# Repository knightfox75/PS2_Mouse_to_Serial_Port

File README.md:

# PS2_Mouse_to_Serial_Port
Un convertidor para conectar un ratón PS/2 a un puerto serie (RS-232).

1. Introducción
--------------------------------------------------------------------------------
Los ratones con conexión DB9 para puerto serie cada vez son más difíciles de encontrar (y más caros), lo que puede suponer un problema si necesitamos emplear uno en un ordenador clásico que solo disponga del puerto serie para su conexión. Después de investigar unas horas, encontré varias opciones comerciales y un par de proyectos open source que, usando placas Arduino, permitían la conexión de un ratón PS/2, o USB compatible con el protocolo PS/2 a un puerto serie.

https://github.com/Lameguy64/ps2serial
 
https://github.com/kristopher/PS2-Mouse-Arduino

Una vez documentado sobre estos proyectos y realizando un primer prototipo funcional de los mismos, decidí realizar mi propia versión del conversor.

2. Como funciona
--------------------------------------------------------------------------------
Básicamente la placa Arduino se encarga de prácticamente todo el trabajo, necesitando solo un poco de electrónica externa para su funcionamiento. Una librería de interacción con el protocolo PS/2 no permite leer la señal codificada procedente del ratón con las entradas. Dicha información se codifica en un paquete de datos en el formato que esperan los drivers de ratón mas comunes y se envían al puerto serie. Además, se monitorea la señal RTS del puerto serie por si se solicita el reinicio del envío de datos.

3. Hardware usado en el prototipo
--------------------------------------------------------------------------------
Se han realizado dos prototipos de prueba, usando las placas Arduino UNO R3 y Arduino NANO, funcionando ambas placas perfectamente. El resto de electrónica sirve para la adaptación de las señales que circulan por el puerto serie, ofreciendo cierto nivel de aislamiento y protección entre este puerto y la placa Arduino. Además, se incorporan dos diodos LED indicadores de estado, para el monitoreo del comportamiento del prototipo.

4. Que indican los LED’s de estado
--------------------------------------------------------------------------------
En mi caso he usado un LED rojo para el indicador de alimentación y un LED amarillo para el indicador de estado. Dicho indicador nos proporciona cierta información en el momento del arranque del adaptador, así como de su funcionamiento. Al encender el adaptador, si no puede detectar un ratón compatible conectado, quedará encendido de manera permanente. Dicho LED de estado parpadeará de manera intermitente una vez por segundo si ha detectado un ratón, pero no es posible iniciar la comunicación siguiendo el protocolo PS/2. Si el proceso de inicio se realiza correctamente, este LED emitirá 3 parpadeos, uno largo seguido de 2 mas cortos. Una vez iniciado el adaptador, si movemos el ratón, observaremos que este LED parpadea regularmente, quedando encendido mientras mantengamos pulsado alguno de los 3 botones del ratón. Si movemos la rueda de scroll, tambien emitira un parpadeo.
Si se recibe desde el puerto serie la señal RTS, este LED emitirá un parpadeo de aproximadamente medio segundo. Esto nos permite verificar que el driver ha detectado correctamente nuestro adaptador.

5. Capacidades extendidas
--------------------------------------------------------------------------------
Dado que este proyecto (en especial la placa ISA) está destinado a ordenadores sin puerto PS/2 (normalmente 486 y anteriores), usando el sistema operativo MS-DOS o Windows 3.11 y anteriores, junto con el hecho de que actualmente casi todos los ratones PS/2 son ópticos y disponen de la rueda de scroll, sumándole que para estos ordenadores casi ningún programa hace uso de la rueda de scroll, he decidido usar dicha rueda para ajustar a tiempo real la velocidad de desplazamiento del cursor. Dado que, según la resolución de pantalla, programa o modelo de ratón esta puede ser diferente, creo que es una característica útil. La velocidad seleccionada se conservará hasta que apaguemos el adaptador (o el ordenador en el caso de la placa ISA), no viendose afectada por el reinicio del sistema. Si queremos guardar la velocidad actual de manera permanente, deberemos de mantener pulsados los botones izquierdo y derecho de manera simultanea durante 5 segundos, observando que el LED de estado se apaga transcurrido ese tiempo. Esto nos indica que la configuración de ha almacenado de manera correcta. Si en algún momento deseamos restaurar la configuración por defecto, deberemos de mantener presionados ambos botones durante 10 segundos, el LED de estado se apagará a los 5 segundos, volviéndose a encender transcurridos 10 segundos. Esto indicará que la configuración se ha restaurado y almacenado con éxito.

6. Precauciones
--------------------------------------------------------------------------------
- Conectar y desconectar siempre el ratón al puerto PS/2 con el adaptador desconectado. La conexión o desconexión del ratón con el adaptador conectado a la alimentación podría causar daños al ratón y al propio adaptador. Esto también se aplica a la conexión del adaptador con el puerto serie del ordenador, siendo muy recomendable que todas las conexiones se realicen con los equipos apagados.
- Cualquier dispositivo conectado al puerto RS-232 del ordenador puede causar daños a dicho puerto o al dispositivo si este tiene algún error de montaje, por lo que se recomienda que repaséis 3 veces las conexiones antes de conectarlo a vuestro ordenador.
- Aplicable a la versión ISA, en ningún caso actualicéis el firmware del modulo Arduino con la tarjeta ISA insertada en la placa base. Retirar la tarjeta ISA o el módulo Arduino antes de conectarlo al puerto USB para su actualización. De no hacerlo, se corre el riesgo de dañar el módulo Arduino la propia placa base del ordenador.

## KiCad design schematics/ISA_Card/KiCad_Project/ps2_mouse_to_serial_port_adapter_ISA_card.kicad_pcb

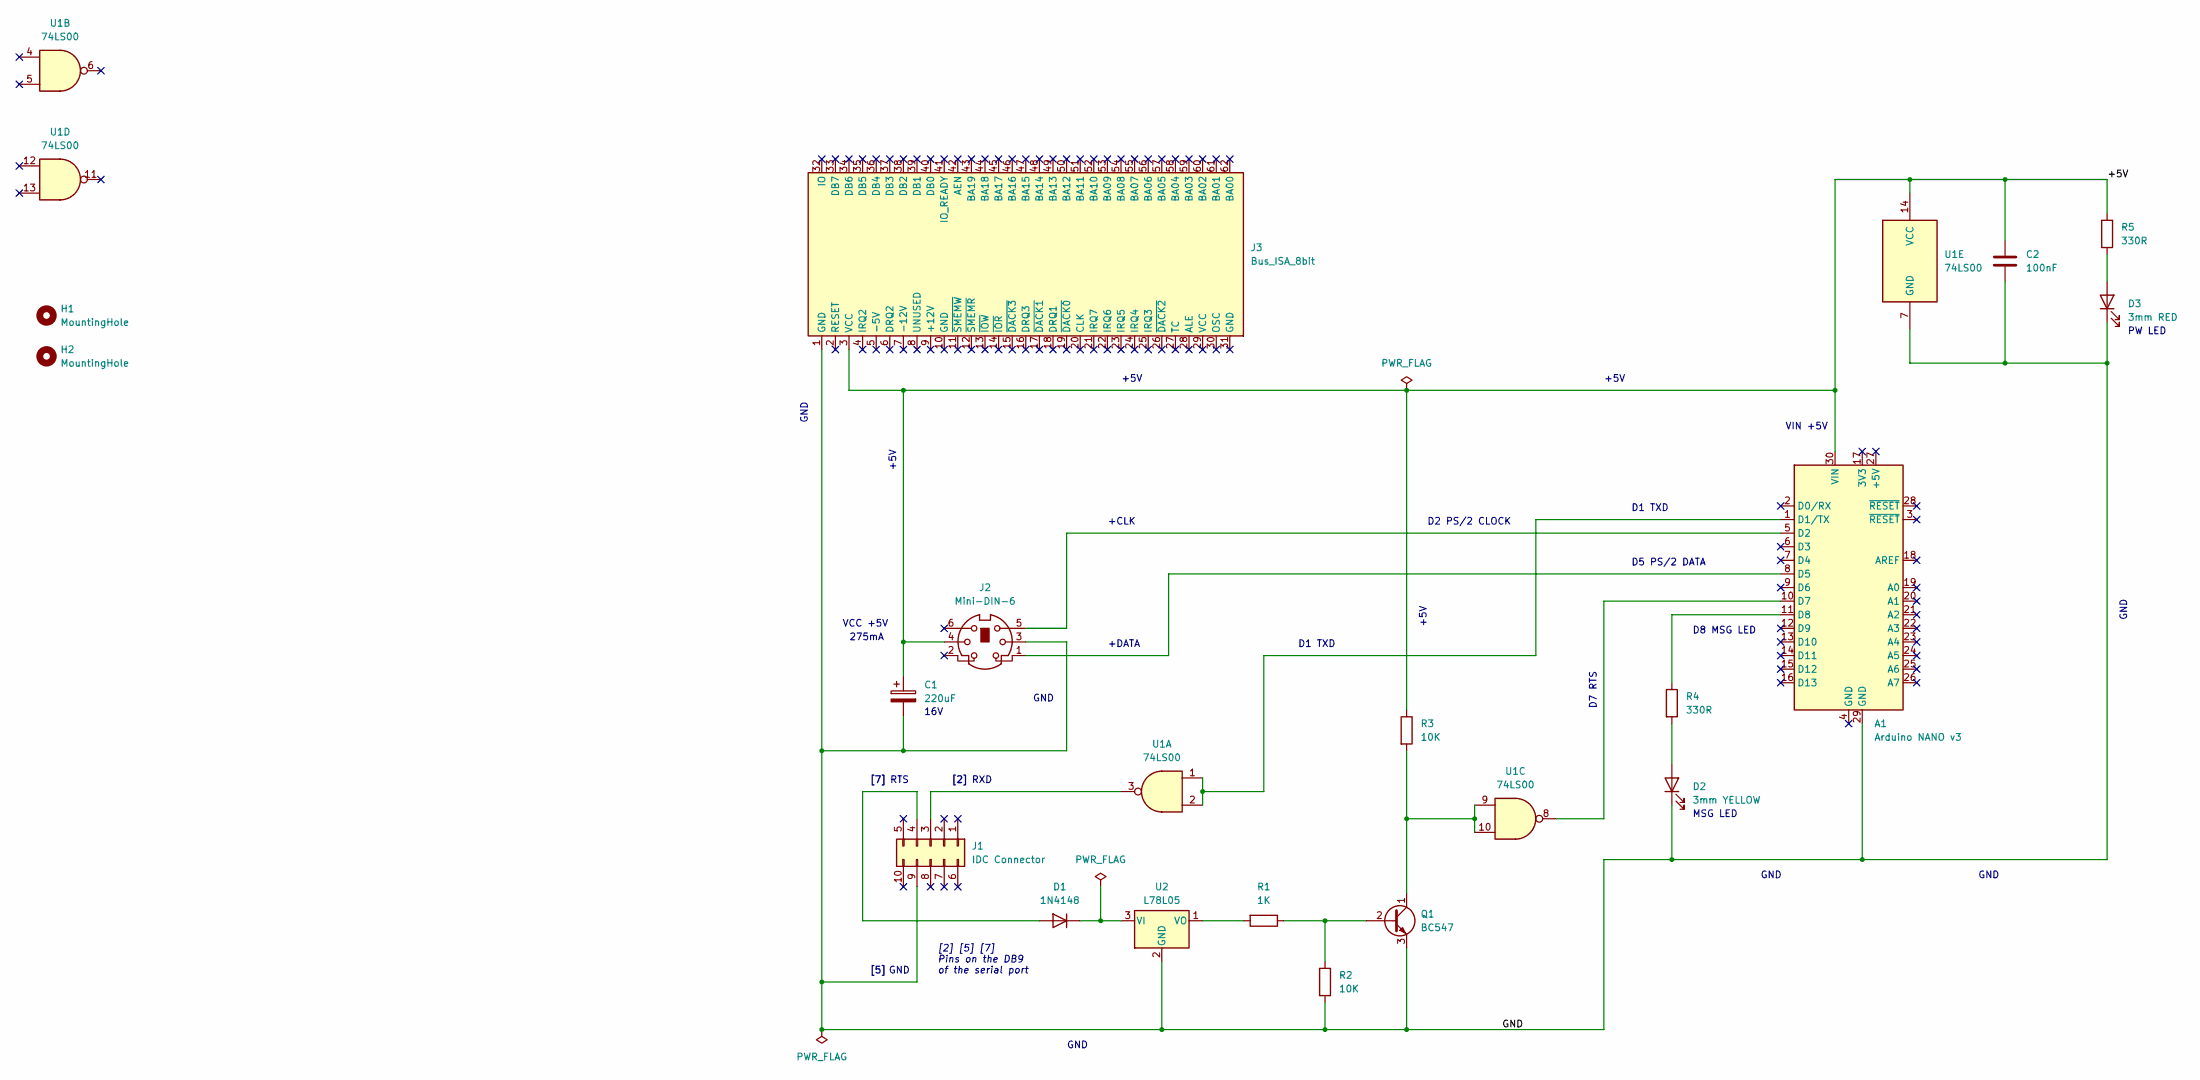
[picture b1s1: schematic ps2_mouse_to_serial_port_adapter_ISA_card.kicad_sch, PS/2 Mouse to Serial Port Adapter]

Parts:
A1: Arduino NANO v3; Arduino_Nano
C1: 220uF; CP_Radial_D8.0mm_P3.80mm
C2: 100nF; C_Disc_D6.0mm_W2.5mm_P5.00mm
D1: 1N4148; D_DO-35_SOD27_P7.62mm_Horizontal
D2: 3mm YELLOW; LED_D3.0mm
D3: 3mm RED; LED_D3.0mm
H1, H2: MountingHole; MountingHole_3.2mm_M3
J1: IDC Connector; IDC-Header_2x05_P2.54mm_Horizontal
J2: Mini-DIN-6; Connector_Mini_DIN_6pin
J3: Bus_ISA_8bit; BUS_AT_ISA_8BITS
Q1: BC547; TO-92_HandSolder
R1: 1K; R_Axial_DIN0207_L6.3mm_D2.5mm_P7.62mm_Horizontal
R2, R3: 10K; R_Axial_DIN0207_L6.3mm_D2.5mm_P7.62mm_Horizontal
R4, R5: 330R; R_Axial_DIN0207_L6.3mm_D2.5mm_P7.62mm_Horizontal
U1: 74LS00; DIP-14_W7.62mm_Socket
U2: L78L05; TO-92_HandSolder

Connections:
/+5V: A1.30 (VIN), C1.1, C2.1, J2.4, J3.3 (VCC), R3.1, R5.1, U1.14 (VCC)
/GND: A1.29 (GND), C1.2, C2.2, D2.1 (K), D3.1 (K), J1.9, J2.3, J2.GND, J3.1 (GND), Q1.3 (E), R2.2, U1.7 (GND), U2.2 (GND)
unnamed: A1.1 (D1/TX), U1.1, U1.2
unnamed: A1.5 (D2), J2.5
unnamed: A1.8 (D5), J2.1
unnamed: A1.10 (D7), U1.8
unnamed: A1.11 (D8), R4.1
unnamed: D1.2 (A), J1.4
unnamed: D1.1 (K), U2.3 (VI)
unnamed: D2.2 (A), R4.2
unnamed: D3.2 (A), R5.2
unnamed: J1.3, U1.3
unnamed: Q1.2 (B), R1.1, R2.1
unnamed: Q1.1 (C), R3.2, U1.9, U1.10
unnamed: R1.2, U2.1 (VO)

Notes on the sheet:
+CLK
PW LED
GND
[5]
[2]
VCC +5V
[2] [5] [7] Pins on the DB9 of the serial port
16V
MSG LED
+5V
D8 MSG LED
RTS
D5 PS/2 DATA
D1 TXD
D2 PS/2 CLOCK
VIN +5V
RXD
D7 RTS
[7]
+DATA
275mA

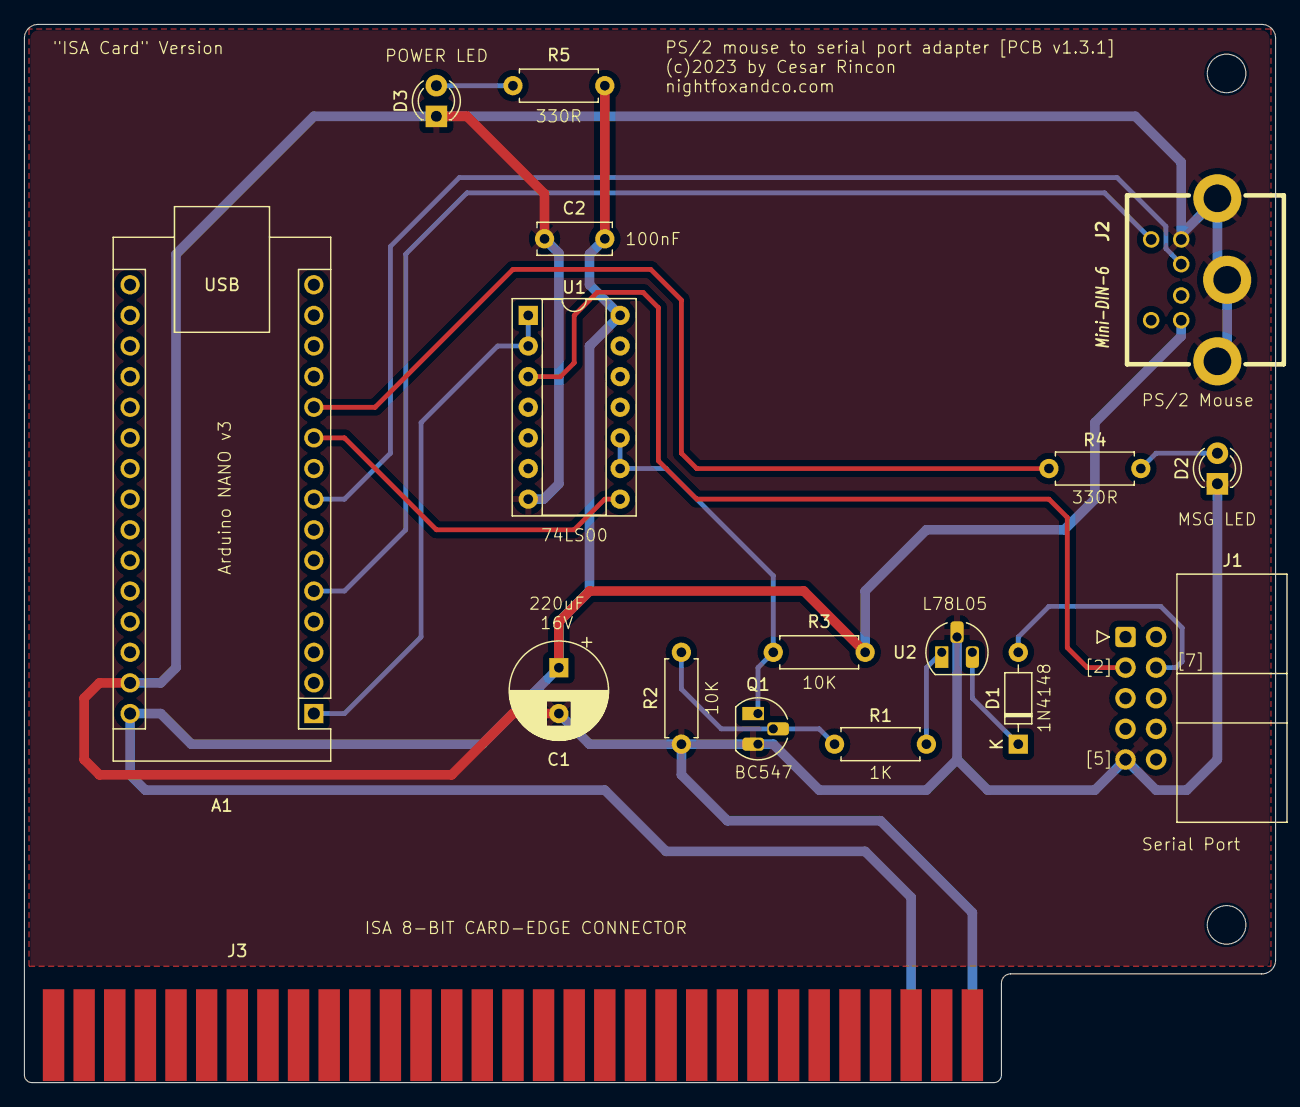
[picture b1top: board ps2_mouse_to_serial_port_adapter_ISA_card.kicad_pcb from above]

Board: 2 copper layers, 103.8 x 87.8 mm, 19 parts (0 on the bottom side), 15 nets.

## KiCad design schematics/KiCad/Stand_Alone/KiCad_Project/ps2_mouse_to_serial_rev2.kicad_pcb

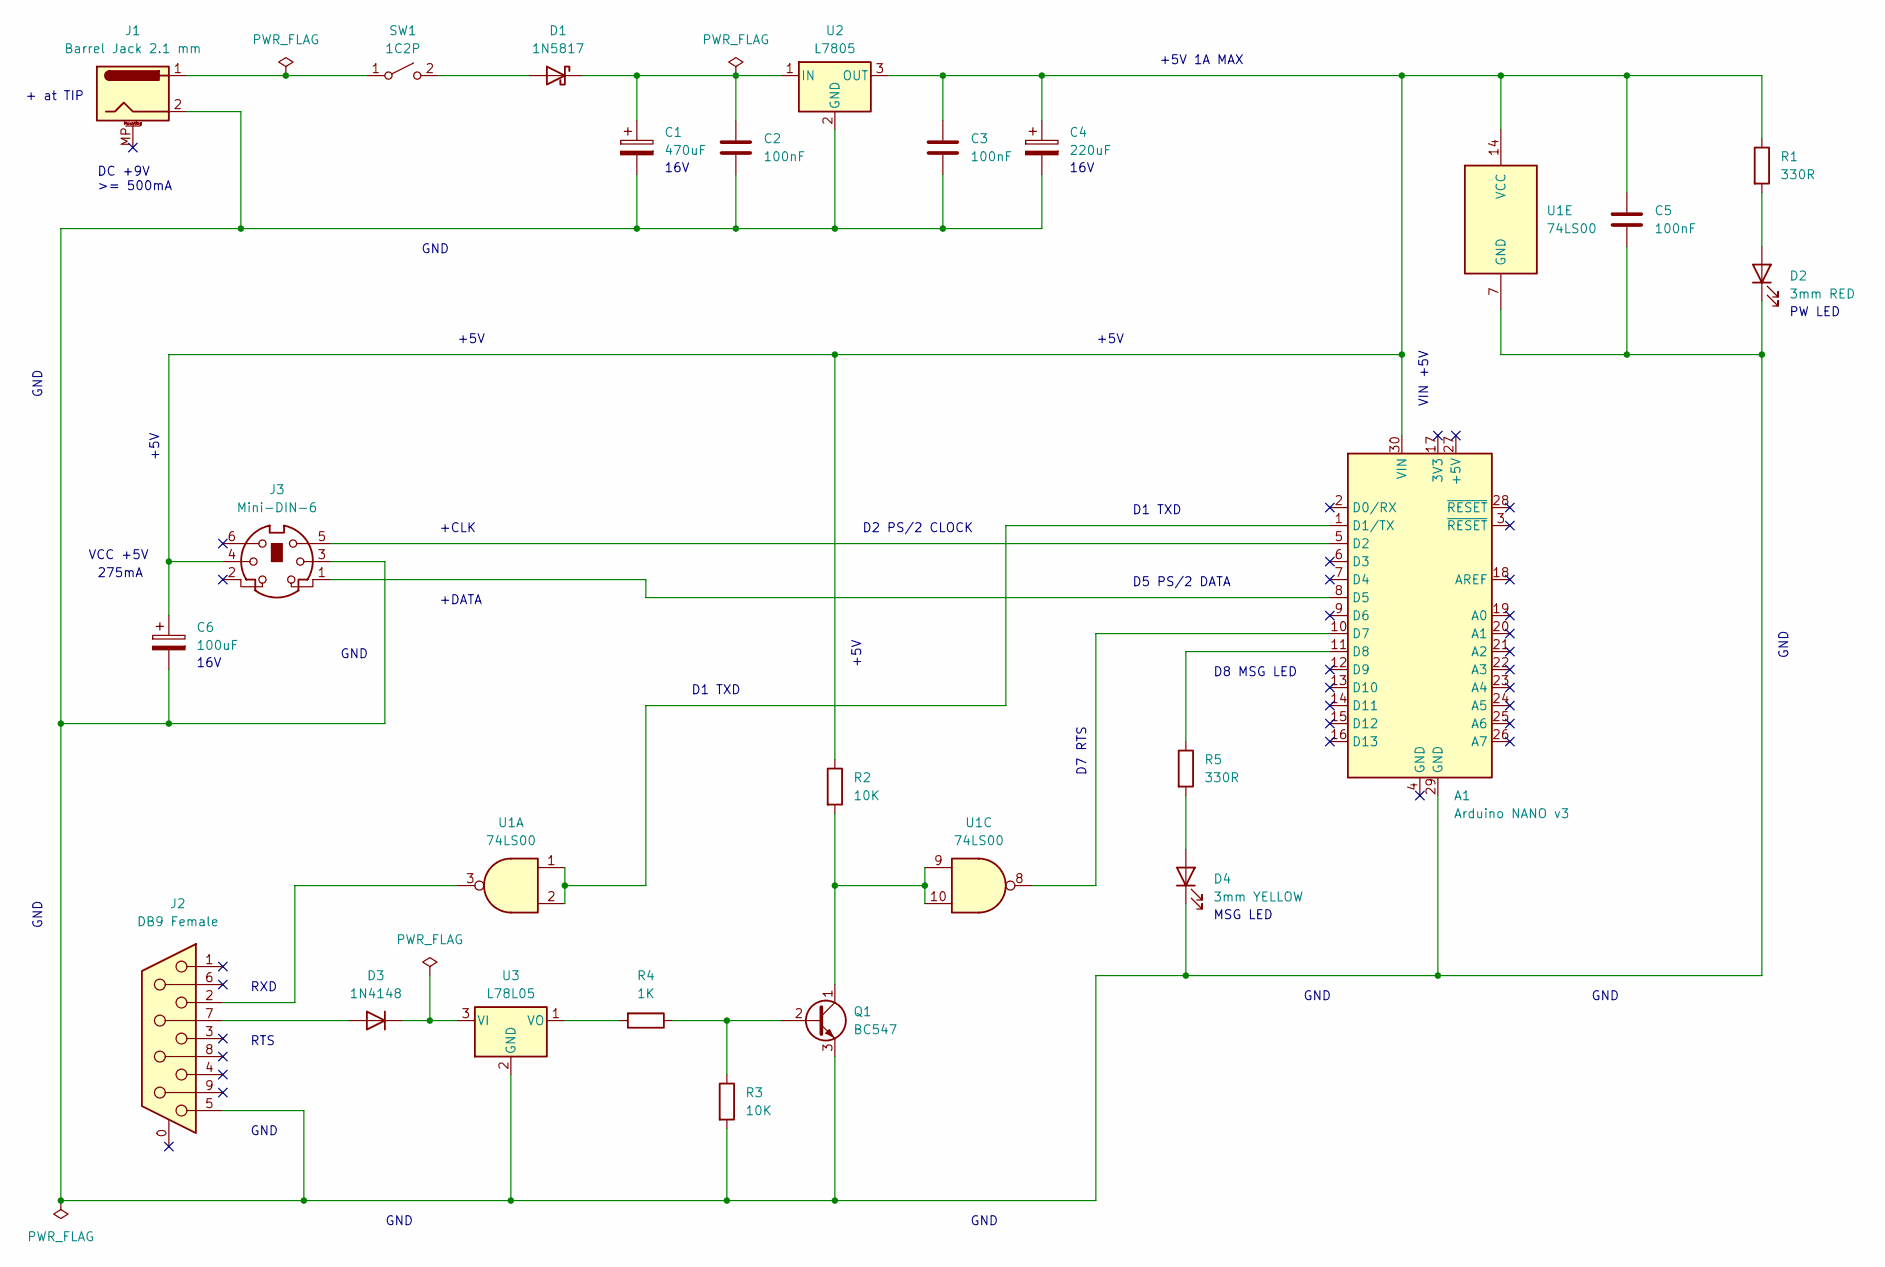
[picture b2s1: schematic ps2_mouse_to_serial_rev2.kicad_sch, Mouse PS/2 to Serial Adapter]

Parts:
A1: Arduino NANO v3; Arduino_Nano
C1: 470uF; CP_Radial_D8.0mm_P3.80mm
C2, C3, C5: 100nF; C_Disc_D6.0mm_W2.5mm_P5.00mm
C4: 220uF; CP_Radial_D8.0mm_P3.80mm
C6: 100uF; CP_Radial_D8.0mm_P3.80mm
D1: 1N5817; D_DO-41_SOD81_P10.16mm_Horizontal
D2: 3mm RED; LED_D3.0mm
D3: 1N4148; D_DO-35_SOD27_P7.62mm_Horizontal
D4: 3mm YELLOW; LED_D3.0mm
J1: Barrel Jack 2.1 mm; BarrelJack_Horizontal
J2: DB9 Female; DSUB-9_Female_Horizontal_P2.77x2.84mm_EdgePinOffset4.94mm_H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
J3: Mini-DIN-6; Conn_Mini_DIN_6pin
Q1: BC547; TO-92_Inline
R1, R5: 330R; R_Axial_DIN0207_L6.3mm_D2.5mm_P7.62mm_Horizontal
R2, R3: 10K; R_Axial_DIN0207_L6.3mm_D2.5mm_P7.62mm_Horizontal
R4: 1K; R_Axial_DIN0207_L6.3mm_D2.5mm_P7.62mm_Horizontal
SW1: 1C2P; TerminalBlock_TE_282834-2_1x02_P2.54mm_Horizontal
U1: 74LS00; DIP-14_W7.62mm_Socket
U2: L7805; TO-220-3_Vertical
U3: L78L05; TO-92_Inline

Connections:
unnamed: A1.1 (D1/TX), U1.1, U1.2
unnamed: A1.5 (D2), J3.5
unnamed: A1.8 (D5), J3.1
unnamed: A1.10 (D7), U1.8
unnamed: A1.11 (D8), R5.1
unnamed: A1.30 (VIN), C3.1, C4.1, C5.1, C6.1, J3.4, R1.1, R2.1, U1.14 (VCC), U2.3 (OUT)
unnamed: D1.2 (A), SW1.2 (B)
unnamed: C1.1, C2.1, D1.1 (K), U2.1 (IN)
unnamed: D2.2 (A), R1.2
unnamed: A1.29 (GND), C1.2, C2.2, C3.2, C4.2, C5.2, C6.2, D2.1 (K), D4.1 (K), J1.2, J2.5, J3.3, Q1.3 (E), R3.2, U1.7 (GND), U2.2 (GND), U3.2 (GND)
unnamed: D3.2 (A), J2.7
unnamed: D3.1 (K), U3.3 (VI)
unnamed: D4.2 (A), R5.2
unnamed: J2.2, U1.3
unnamed: Q1.2 (B), R3.1, R4.1
unnamed: Q1.1 (C), R2.2, U1.9, U1.10
unnamed: J1.1, SW1.1 (A)
unnamed: R4.2, U3.1 (VO)

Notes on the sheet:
+CLK
PW LED
GND
16V
VCC +5V
MSG LED
+5V
D8 MSG LED
DC +9V >= 500mA
RTS
D5 PS/2 DATA
D1 TXD
D2 PS/2 CLOCK
+ at TIP
VIN +5V
RXD
D7 RTS
+5V 1A MAX
+DATA
275mA

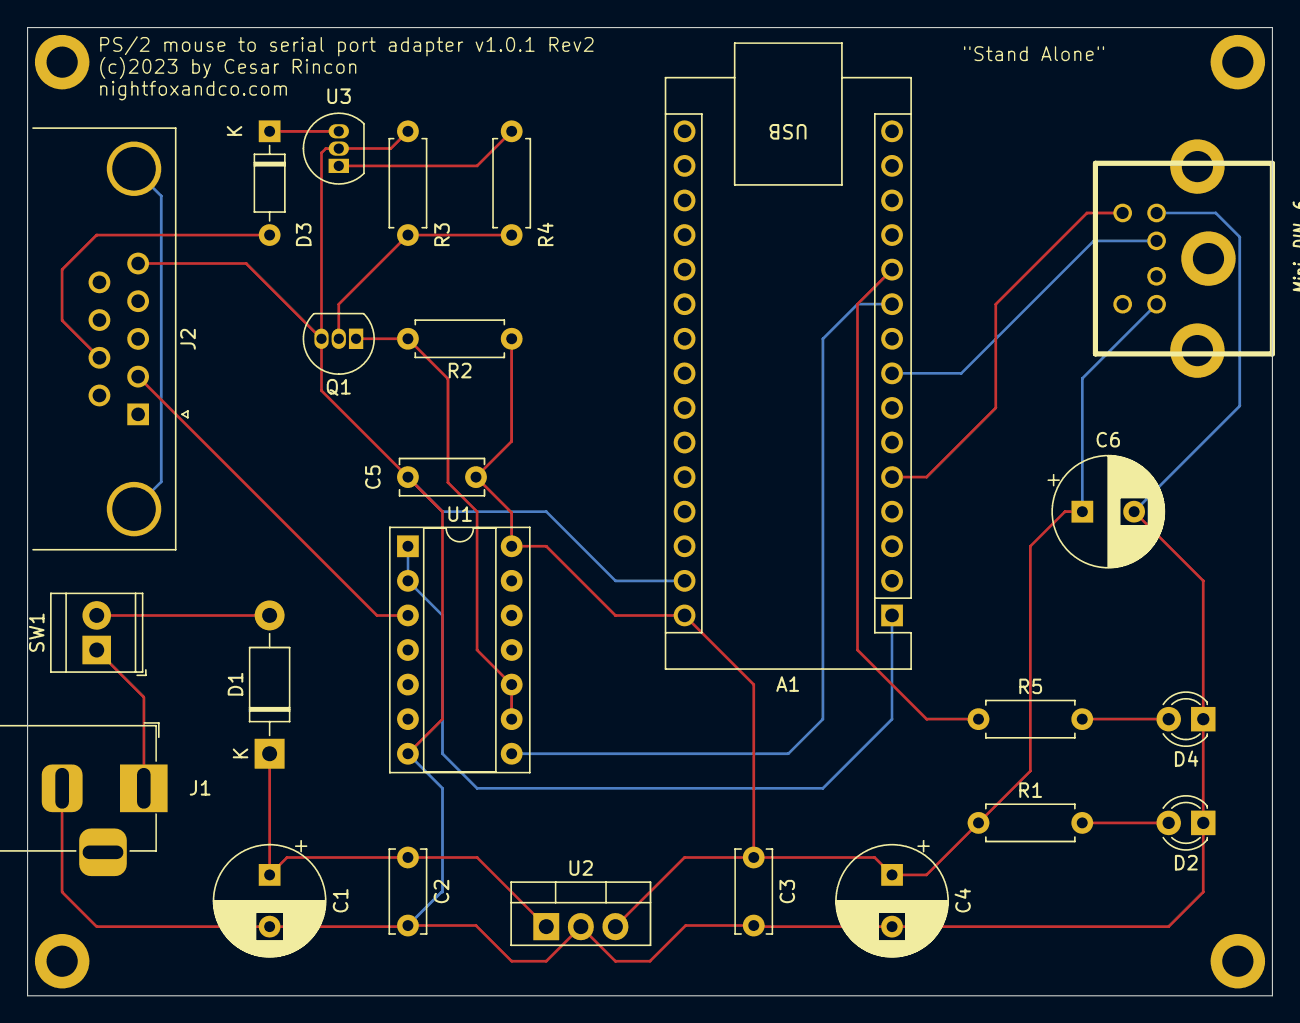
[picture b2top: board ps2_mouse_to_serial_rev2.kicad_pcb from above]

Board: 2 copper layers, 91.4 x 71.1 mm, 24 parts (0 on the bottom side), 18 nets.

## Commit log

2023-07-26 PS/2 Mouse to Serial v0.9.0-beta
    Initial release.
2023-08-08 V1.0.0-stable
    - Modificado el esquema, añadiendo una fuente de alimentación opcional y un diodo de protección en la entrada de la señal RTS del puerto serie.
    - No hay cambios en el código.
    - Verificado el funcionamiento del prototipo con éxito en los siguientes
    equipos y configuraciones:
    · Amstrad PC1512, MS-DOS 6.22, CuteMouse 1.91 & MS Mouse 11
    · Philips NMS9100, MS-DOS 6.22, CuteMouse 1.91 & MS Mouse 11
2023-08-09 V1.0.1-rev2
    - Se añade el esquema realizado en formato KiCad.
    - Corregido un error en la conexión a masa del condensador C6 en el esquema en formato TinyCad.
    - Modificadas algunas de las anotaciones en los pins de Arduino en el esquema en formato TinyCad.
    - Añadidos los esquemas de KiCad en formato PDF y PNG.
    - No hay cambios en el código.
2023-08-10 v1.0.1-rev2
    - Se añade el esquema realizado en formato KiCad.
    - Corregido un error en la conexión a masa del condensador C6 en el esquema en formato TinyCad.
    - Modificadas algunas de las anotaciones en los pins de Arduino en el esquema en formato TinyCad.
    - Añadidos los esquemas de KiCad en formato PDF y PNG.
    - Añadidos los diseños de las PBC para las version "Stand Alone" y "In-a-Box". Estos diseños se han mandado a producción, pero aún no se han verificado.
    - No hay cambios en el código.
2023-08-11 V1.0.1-rev2.1
    - Corregido un error en la colocación del conector PS/2 en la placa "Stand Alone" del proyecto KiCad.
    - Recordar que aún no he podido producir físicamente estas placas, por lo que si vais a producirlas, revisar el proyecto 3 veces en búsqueda de errores.
2023-08-12 v1.3.0
    - Se utiliza una referencia de versión para el proyecto, independientemente de las versiones de placa o software para facilitar la identificación de la versión actual.
    - Se añade el esquema y diseño de placa para la versión "ISA".
    - Se amplía el ancho de pista en las placas restantes.
    - Sin cambios en el software.
    - Importante! Recordad que aún no he podido verificar en "físico" el diseño de las placas, por lo que recomiendo precaución si van a ser usadas.
2023-08-12 v1.4.0
    - Pequeños ajustes al tamaño y contorno de la placa ISA.
    - Se han añadido zonas de relleno para GND en la placa ISA.
    - Sin cambios en el software.
    - Importante! Recordad que aún no he podido verificar en "físico" el diseño de las placas, por lo que recomiendo precaución si van a ser usadas.
2023-08-13 v1.5.0
    - Ajustadas las placas "Stand alone" y "In-a-box" al tamaño standard de
    90x70 mm.
    - Añadidas a estas placas las zonas de relleno a masa (GND).
    - Añadidas las serigrafias con los valores de todos los componentes en todas
    las versiones de las placas.
2023-08-14 v1.5.1
    - Arreglada la serigrafía del conector MINI-DIN-6 (PS/2), la cual se superponía en algunas zonas de soldado.
    - En todas las placas se añade el símbolo de los agujeros de montaje con el tamaño estándar M3.
2023-08-24 v1.6.0
    Modificada la librería PS2Mouse para evitar que la placa Arduino se quede colgada al iniciarse si no se detecta el mouse conectado en el puerto PS/2.
    Ahora si la inicialización del mouse falla, se reescanea el puerto a cada segundo.
    De todos modos, os recomiendo que no conectéis o desconectéis el mouse con el adaptador/ordenador encendido, ya que hay la posibilidad de que se causen daños al adaptador o al propio mouse.
2023-08-28 v1.7.0
    - Modificadas las huellas de todas las placas para que los componentes TO92 resulten más fáciles de soldar a mano.
    - Modificadas las conexiones del conector IDC en la placa ISA para poder usar un cable IDC a DB9 comercial, sin necesidad de realizarle modificaciones.
    - Añadido el modelo en formato FreeCad y el archivo STL del soporte para la placa ISA. Estos archivos estan preparados para poder realizar la impresión en 3D del soporte. Se recomienda un in-fill del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
2023-08-29 v1.7.1
    - Modificado el ancho de la pista de alimentación del puerto PS/2 de la placa ISA.
2023-08-29 v1.7.1
    - Wrong files upload fix.
2023-09-06 v1.8.0
    - Dado que algunos modelos de ratón no funcionaban como es debido y en algunos casos ni encendían (PERIMICE-209), se analiza la librería usada de Arduino para la interfaz con el puerto PS/2. Viendo q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
    - Ahora todos los comandos que se envían al ratón se verifican.
    - Se añade una secuencia de encendido para activar algunos modelos de ratón que antes no funcionaban, como el PERIMICE-209.
    - Con la librería personalizada, se añade la opción de detectar si el ratón es compatible con Microsoft IntelliMouse y este

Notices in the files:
schematics/ISA_Card/KiCad_Project/ps2_mouse_to_serial_port_adapter_ISA_card.kicad_pcb:
(c)2023 by Cesar Rincon
